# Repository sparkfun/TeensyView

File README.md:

SparkFun TeensyView
========================================

[*SparkFun TeensyView (LCD-14048)*](https://www.sparkfun.com/products/14048)

An OLED display for the Teensy 3

Repository Contents
-------------------

* **/Hardware** - Eagle design files (.brd, .sch)
* **/Libraries** - Libraries for use with the TeensyView
* **/Production** - Production panel files (.brd)

Documentation
--------------
* **[Library](https://github.com/sparkfun/SparkFun_TeensyView_Arduino_Library/)** - C++ library for the TeensyView.
* **[Hookup Guide](https://learn.sparkfun.com/tutorials/teensyview-hookup-guide)** - Basic hookup guide for the TeensyView.
* **[SparkFun Fritzing repo](https://github.com/sparkfun/Fritzing_Parts)** - Fritzing diagrams for SparkFun products.
* **[SparkFun 3D Model repo](https://github.com/sparkfun/3D_Models)** - 3D models of SparkFun products. 
* **[SparkFun Graphical Datasheets](https://github.com/sparkfun/Graphical_Datasheets)** -Graphical Datasheets for various SparkFun products.

Product Versions
---------------------------------

* [LCD-14048](https://www.sparkfun.com/products/14048) - TeensyView product.

Compatible products
---------------------------------

* [DEV-13305](https://www.sparkfun.com/products/13305) - Teensy LC
* [DEV-13736](https://www.sparkfun.com/products/13736) - Teensy 3.2
* [DEV-14055](https://www.sparkfun.com/products/14055) - Teensy 3.5
* [DEV-14057](https://www.sparkfun.com/products/14057) - Teensy 3.6
* [DEV-12767](https://www.sparkfun.com/products/12767) - Teensy Audio Board
* [BOB-13311](https://www.sparkfun.com/products/13311) - Teensy 3.1 XBee Adapter
* [PRT-13925](https://www.sparkfun.com/products/13925) - Teensy Header Kit
* [DEV-13996](https://www.sparkfun.com/products/13996) - Teensy Prop Shield LC
* [DEV-13995](https://www.sparkfun.com/products/13995) - Teensy Prop Shield

Version History
---------------
* [V_1.0.0](https://github.com/sparkfun/TeensyView/tree/V_1.0.0) - Initial release

License Information
-------------------

This product is _**open source**_! 

Please review the LICENSE.md file for license information. 

If you have any questions or concerns on licensing, please contact techsupport@sparkfun.com.

Distributed as-is; no warranty is given.

- Your friends at SparkFun.

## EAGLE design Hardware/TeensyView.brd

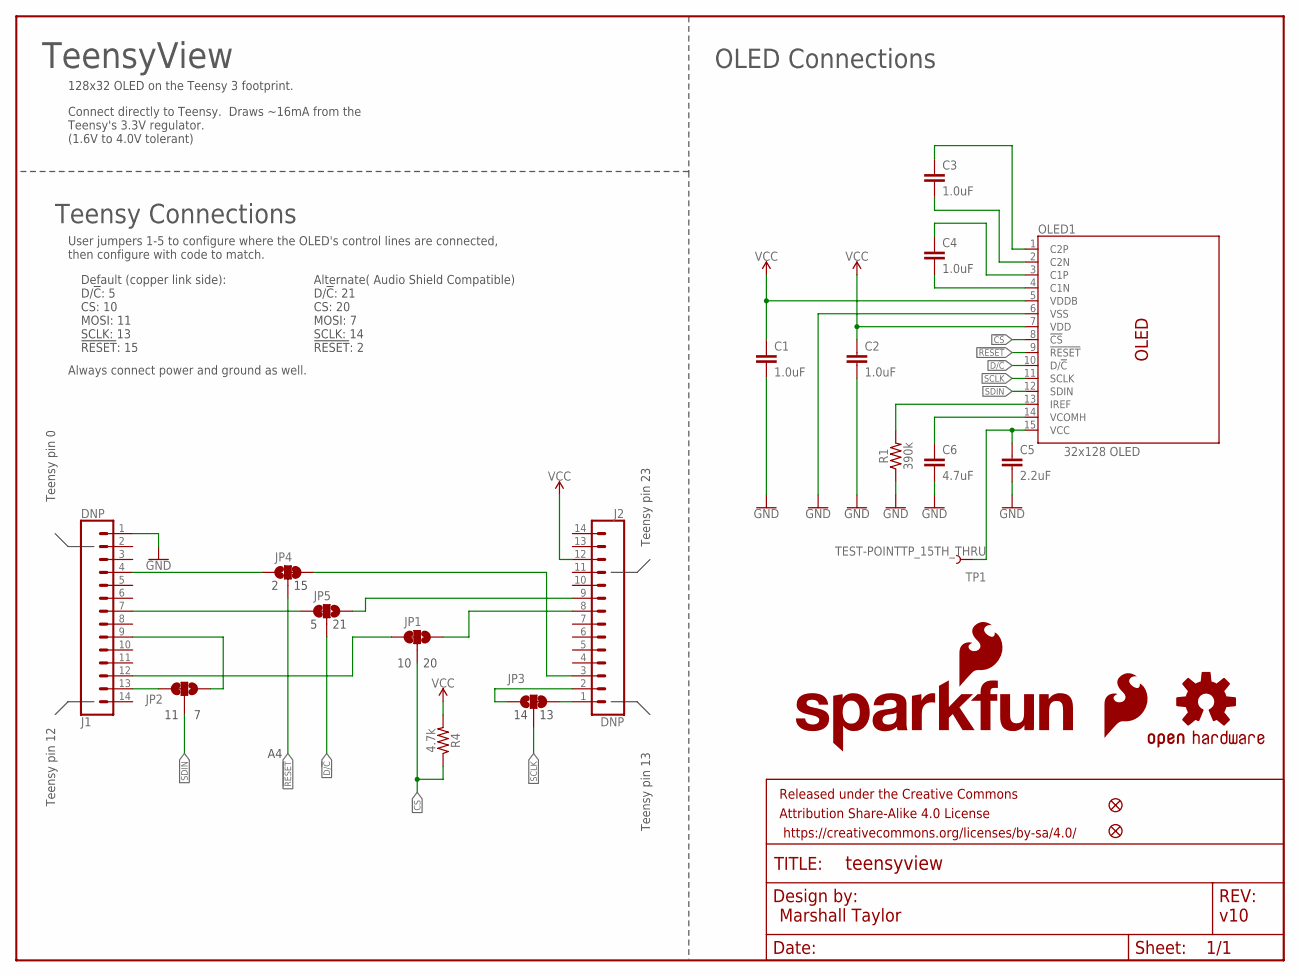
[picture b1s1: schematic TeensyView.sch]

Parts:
C1, C2, C3, C4: 1.0uF; 0402
C5: 2.2uF; 0805
C6: 4.7uF; 1206
FD1, FD2: FIDUCIALUFIDUCIAL; FIDUCIAL-MICRO
FRAME1: FRAME-LETTER; CREATIVE_COMMONS
J1, J2: DNP; 1X14_NO_SILK
JP1, JP2, JP3, JP4, JP5: JUMPER-SMT_3_1-NC_TRACE_SILK; SMT-JUMPER_3_1-NC_TRACE_SILK
LOGO1: SFE_LOGO_FLAME.1_INCH; SFE_LOGO_FLAME_.1
LOGO2: OSHW-LOGOS; OSHW-LOGO-S
LOGO3: SFE_LOGO_NAME_FLAME.1_INCH; SFE_LOGO_NAME_FLAME_.1
OLED1: 32x128 OLED; OLED-UG-2832TSWGG01-REAR
R1: 390k; 0603
R4: 4.7k; 0603
TP1: TEST-POINTTP_15TH_THRU; TP_15TH

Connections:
!CS: JP1.2, OLED1.8 (!CS!), R4.1
!RESET: JP4.2, OLED1.9 (!RESET!)
D/!C: JP5.2, OLED1.10 (D/!C!)
GND: C1.2, C2.2, C5.2, C6.2, J1.1, OLED1.6 (VSS), R1.1
unnamed: J1.12, JP1.3
unnamed: J2.8, JP1.1
unnamed: C4.2, OLED1.4 (C1N)
unnamed: C4.1, OLED1.3 (C1P)
unnamed: C3.2, OLED1.2 (C2N)
unnamed: C3.1, OLED1.1 (C2P)
unnamed: OLED1.13 (IREF), R1.2
unnamed: C6.1, OLED1.14 (VCOMH)
unnamed: C5.1, OLED1.15 (VCC), TP1.P$1
unnamed: J2.1, JP3.3
unnamed: J2.2, JP3.1
unnamed: J1.13, JP2.3
unnamed: J1.9, JP2.1
unnamed: J2.3, JP4.3
unnamed: J1.4, JP4.1
unnamed: J1.7, JP5.3
unnamed: J2.9, JP5.1
SCLK: JP3.2, OLED1.11 (SCLK)
SDIN: JP2.2, OLED1.12 (SDIN)
VCC: C1.1, C2.1, J2.12, OLED1.5 (VDDB), OLED1.7 (VDD), R4.2

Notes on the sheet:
v10
Marshall Taylor
Teensy pin 0
Teensy pin 12
Teensy pin 13
Teensy pin 23
128x32 OLED on the Teensy 3 footprint.
User jumpers 1-5 to configure where the OLED's control lines are connected, then configure with code to match.
TeensyView
Connect directly to Teensy. Draws ~16mA from the Teensy's 3.3V regulator. (1.6V to 4.0V tolerant)
Teensy Connections
OLED Connections
Default (copper link side): D/!C!: 5 CS: 10 MOSI: 11 SCLK: 13 !RESET!: 15
Alternate( Audio Shield Compatible) D/!C!: 21 CS: 20 MOSI: 7 SCLK: 14 !RESET!: 2
Always connect power and ground as well.

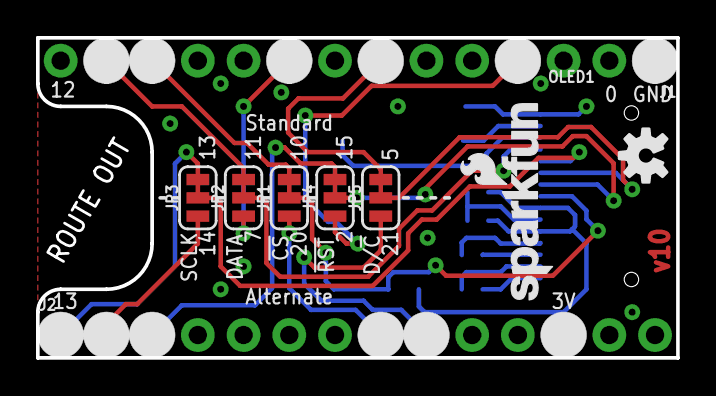
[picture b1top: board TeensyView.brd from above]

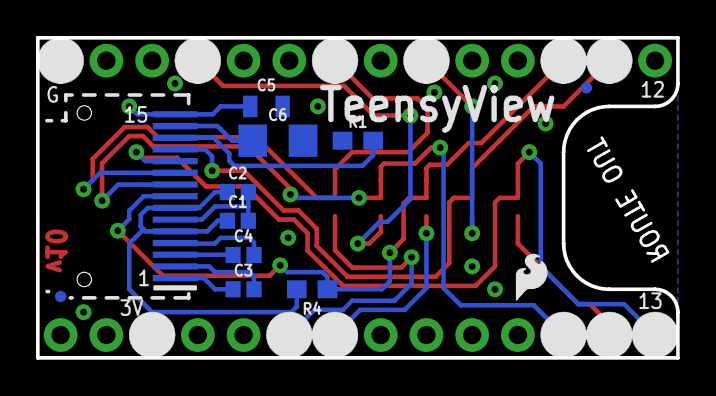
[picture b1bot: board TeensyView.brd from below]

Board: 2 copper layers, 35.6 x 17.8 mm, 23 parts (12 on the bottom side), 24 nets.

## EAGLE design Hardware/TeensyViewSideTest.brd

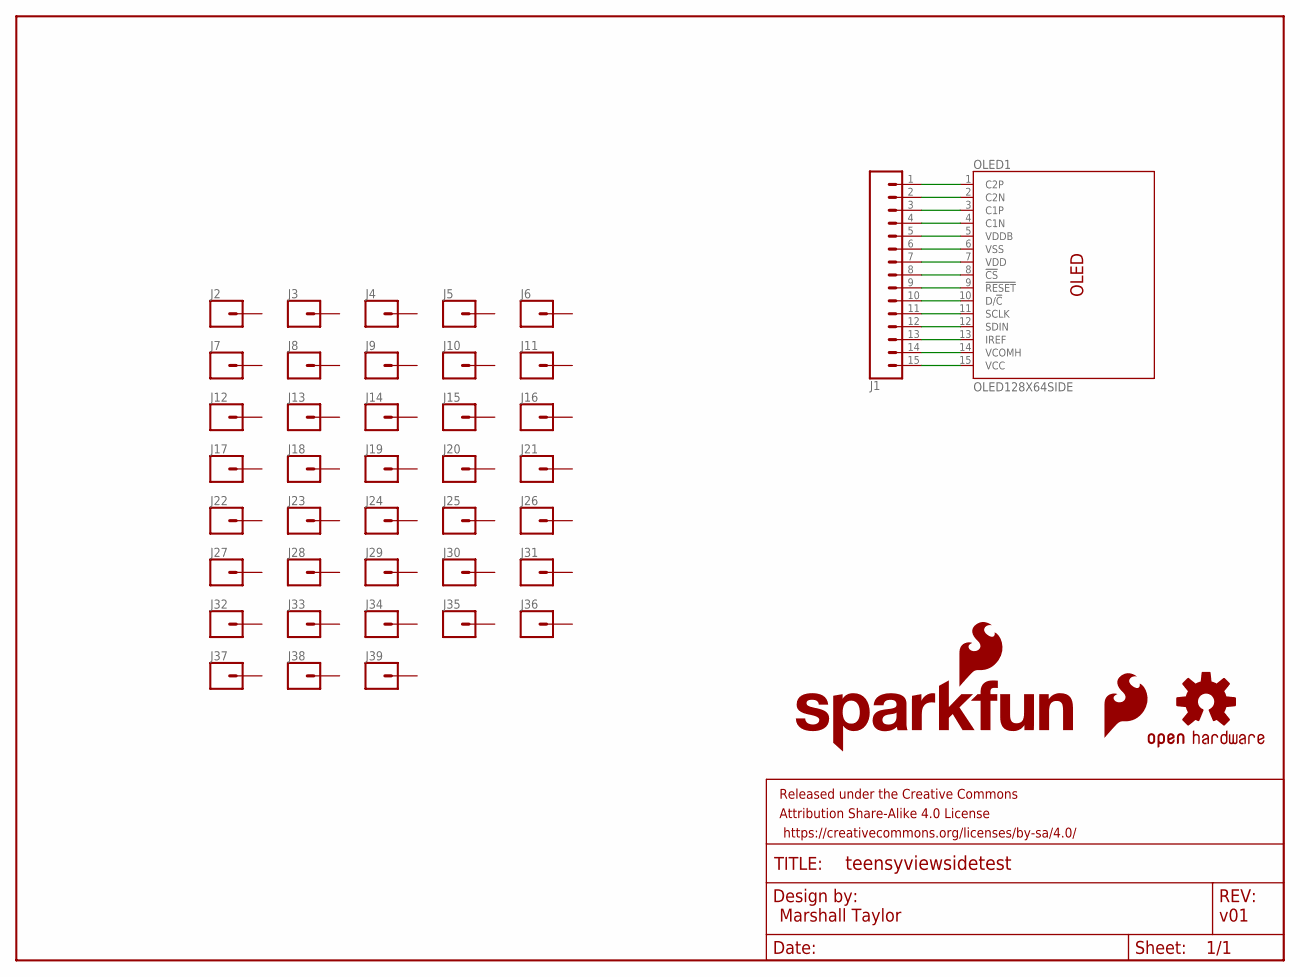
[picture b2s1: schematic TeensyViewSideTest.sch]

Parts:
FRAME1: FRAME-LETTER; CREATIVE_COMMONS
J1: CONN_15; 1X15
J2, J3, J4, J5, J6, J7, J8, J9, J10, J11, J12, J13, J14, J15, J16, J17, J18, J19, J20, J21, J22, J23, J24, J25, J26, J27, J28, J29, J30, J31, J32, J33, J34, J35, J36, J37, J38, J39: CONN_01PTH_NO_SILK_YES_STOP; 1X01_NO_SILK
LOGO1: SFE_LOGO_FLAME.1_INCH; SFE_LOGO_FLAME_.1
LOGO2: OSHW-LOGOS; OSHW-LOGO-S
LOGO3: SFE_LOGO_NAME_FLAME.1_INCH; SFE_LOGO_NAME_FLAME_.1
OLED1: OLED128X64SIDE; OLED-UG-2832TSWGG01

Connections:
unnamed: J1.1, OLED1.1 (C2P)
unnamed: J1.2, OLED1.2 (C2N)
unnamed: J1.3, OLED1.3 (C1P)
unnamed: J1.4, OLED1.4 (C1N)
unnamed: J1.5, OLED1.5 (VDDB)
unnamed: J1.6, OLED1.6 (VSS)
unnamed: J1.7, OLED1.7 (VDD)
unnamed: J1.8, OLED1.8 (!CS!)
unnamed: J1.9, OLED1.9 (!RESET!)
unnamed: J1.10, OLED1.10 (D/!C!)
unnamed: J1.11, OLED1.11 (SCLK)
unnamed: J1.12, OLED1.12 (SDIN)
unnamed: J1.13, OLED1.13 (IREF)
unnamed: J1.14, OLED1.14 (VCOMH)
unnamed: J1.15, OLED1.15 (VCC)

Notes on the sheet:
v01
Marshall Taylor

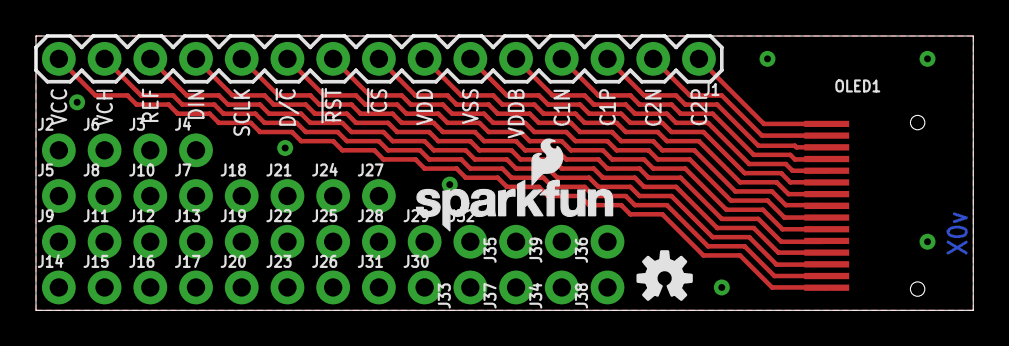
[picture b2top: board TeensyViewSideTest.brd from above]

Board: 2 copper layers, 52.1 x 15.2 mm, 44 parts (1 on the bottom side), 15 nets.

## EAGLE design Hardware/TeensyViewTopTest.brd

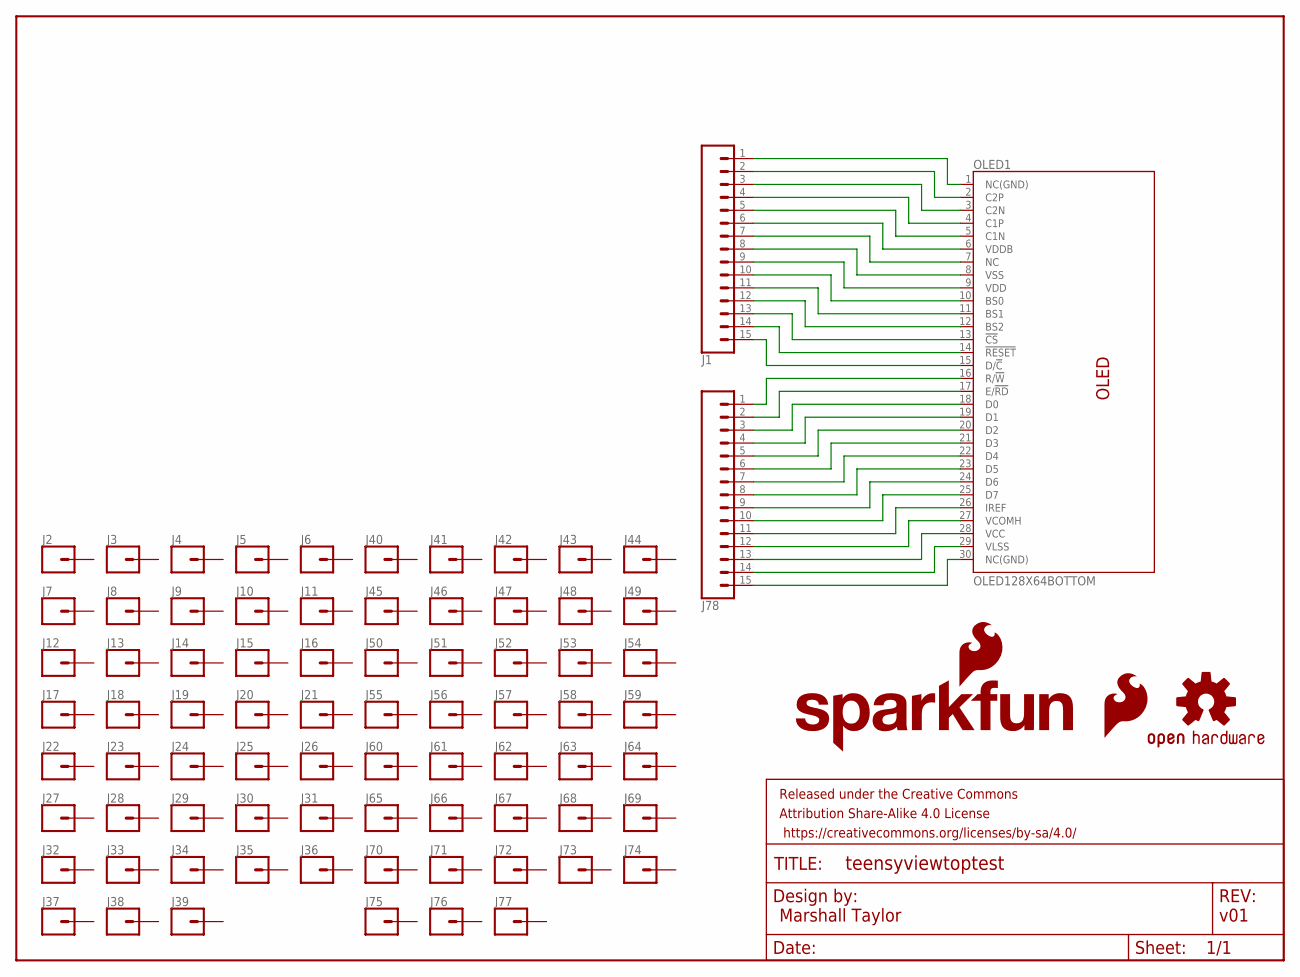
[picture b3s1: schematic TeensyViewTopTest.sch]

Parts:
FRAME1: FRAME-LETTER; CREATIVE_COMMONS
J1, J78: CONN_15; 1X15
J2, J3, J4, J5, J6, J7, J8, J9, J10, J11, J12, J13, J14, J15, J16, J17, J18, J19, J20, J21, J22, J23, J24, J25, J26, J27, J28, J29, J30, J31, J32, J33, J34, J35, J36, J37, J38, J39, J40, J41, J42, J43, J44, J45, J46, J47, J48, J49, J50, J51, J52, J53, J54, J55, J56, J57, J58, J59, J60, J61, J62, J63, J64, J65, J66, J67, J68, J69, J70, J71, J72, J73, J74, J75, J76, J77: CONN_01PTH_NO_SILK_YES_STOP; 1X01_NO_SILK
LOGO1: SFE_LOGO_FLAME.1_INCH; SFE_LOGO_FLAME_.1
LOGO2: OSHW-LOGOS; OSHW-LOGO-S
LOGO3: SFE_LOGO_NAME_FLAME.1_INCH; SFE_LOGO_NAME_FLAME_.1
OLED1: OLED128X64BOTTOM; OLED-UG-2832HLBEG04

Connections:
unnamed: J1.1, OLED1.1 (NC(GND))
unnamed: J1.2, OLED1.2 (C2P)
unnamed: J1.3, OLED1.3 (C2N)
unnamed: J1.4, OLED1.4 (C1P)
unnamed: J1.5, OLED1.5 (C1N)
unnamed: J1.6, OLED1.6 (VDDB)
unnamed: J1.7, OLED1.7 (NC)
unnamed: J1.8, OLED1.8 (VSS)
unnamed: J1.9, OLED1.9 (VDD)
unnamed: J1.10, OLED1.10 (BS0)
unnamed: J1.11, OLED1.11 (BS1)
unnamed: J1.12, OLED1.12 (BS2)
unnamed: J1.13, OLED1.13 (!CS!)
unnamed: J1.14, OLED1.14 (!RESET!)
unnamed: J1.15, OLED1.15 (D/!C!)
unnamed: J78.1, OLED1.16 (R/!W!)
unnamed: J78.2, OLED1.17 (E/!RD!)
unnamed: J78.3, OLED1.18 (D0)
unnamed: J78.4, OLED1.19 (D1)
unnamed: J78.5, OLED1.20 (D2)
unnamed: J78.6, OLED1.21 (D3)
unnamed: J78.7, OLED1.22 (D4)
unnamed: J78.8, OLED1.23 (D5)
unnamed: J78.9, OLED1.24 (D6)
unnamed: J78.10, OLED1.25 (D7)
unnamed: J78.11, OLED1.26 (IREF)
unnamed: J78.12, OLED1.27 (VCOMH)
unnamed: J78.13, OLED1.28 (VCC)
unnamed: J78.14, OLED1.29 (VLSS)
unnamed: J78.15, OLED1.30 (NC(GND))

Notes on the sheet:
v01
Marshall Taylor

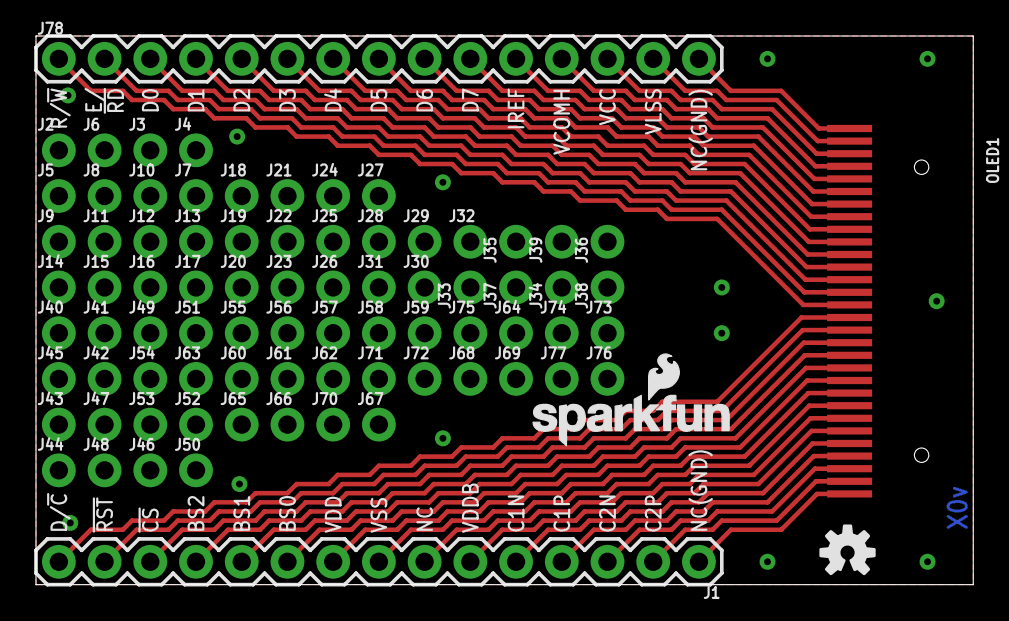
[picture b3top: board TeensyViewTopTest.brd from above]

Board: 2 copper layers, 52.1 x 30.5 mm, 83 parts (1 on the bottom side), 30 nets.

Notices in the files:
parts and their libraries:
SparkFun-Aesthetics: Licensing: Creative Commons ShareAlike 4.0 International - https://creativecommons.org/licenses/by-sa/4.0
SparkFun-Aesthetics: Released under the Creative Commons Attribution Share-Alike 4.0 License
SparkFun-Aesthetics: https://creativecommons.org/licenses/by-sa/4.0
